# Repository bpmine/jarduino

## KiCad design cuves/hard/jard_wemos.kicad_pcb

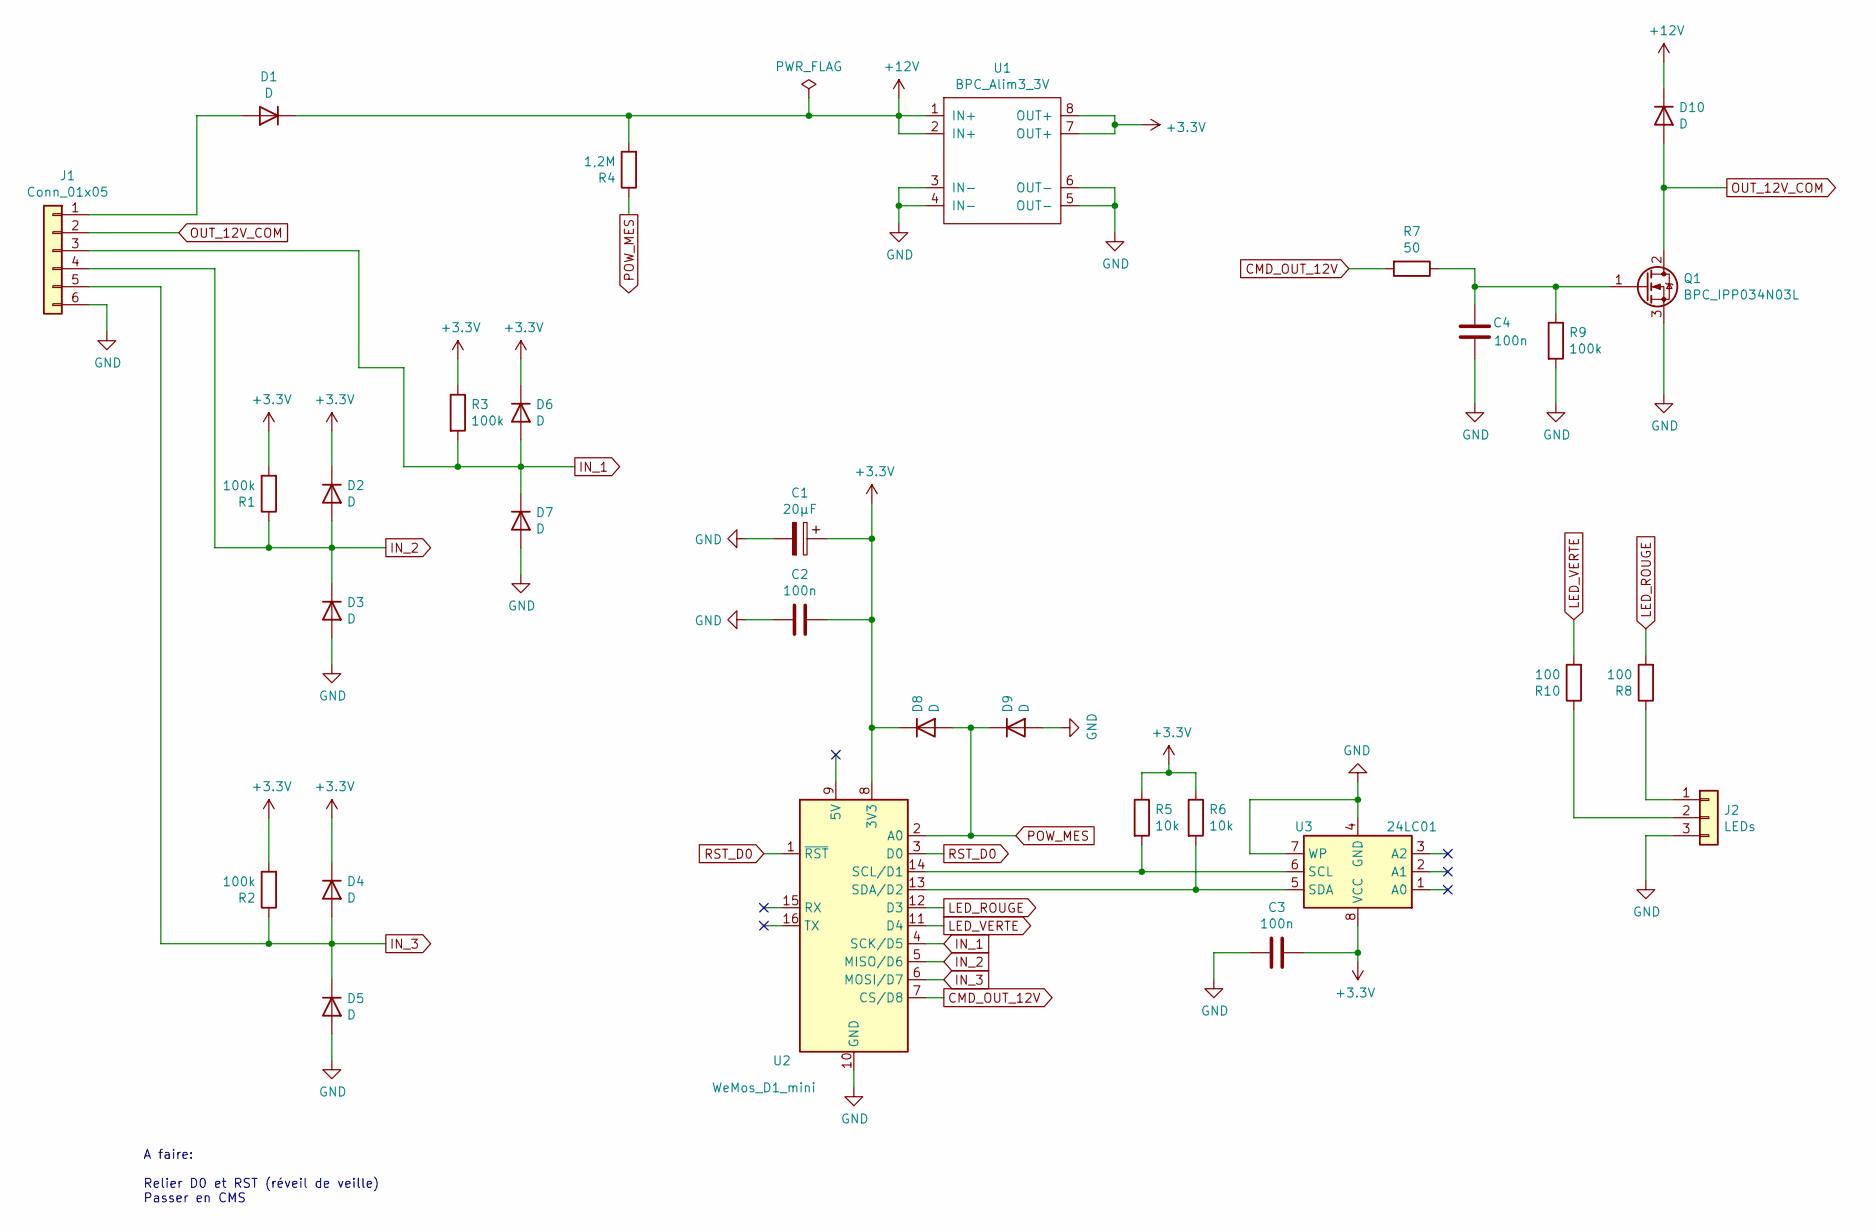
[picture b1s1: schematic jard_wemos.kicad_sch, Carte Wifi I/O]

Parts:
C1: 20µF; C_Radial_D6.3mm_H7.0mm_P2.50mm
C2, C3, C4: 100n; C_Disc_D3.0mm_W2.0mm_P2.50mm
D1, D2, D3, D4, D5, D6, D7, D8, D9, D10: D; D_A-405_P2.54mm_Vertical_KathodeUp
J1: Conn_01x05; TerminalBlock_Phoenix_MPT-0,5-6-2.54_1x06_P2.54mm_Horizontal
J2: LEDs; PinHeader_1x03_P2.54mm_Vertical
Q1: BPC_IPP034N03L; TO-220-3_Vertical
R1, R2, R3, R9: 100k; R_Axial_DIN0207_L6.3mm_D2.5mm_P2.54mm_Vertical
R4: 1,2M; R_Axial_DIN0207_L6.3mm_D2.5mm_P2.54mm_Vertical
R5, R6: 10k; R_Axial_DIN0207_L6.3mm_D2.5mm_P2.54mm_Vertical
R7: 50; R_Axial_DIN0207_L6.3mm_D2.5mm_P2.54mm_Vertical
R8, R10: 100; R_Axial_DIN0207_L6.3mm_D2.5mm_P2.54mm_Vertical
U1: BPC_Alim3_3V
U2: WeMos_D1_mini; WEMOS_D1_mini_light
U3: 24LC01; DIP-8_W7.62mm

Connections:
+3V3: C1.1, C2.1, C3.2, D2.1 (K), D4.1 (K), D6.1 (K), D8.1 (K), R1.2, R2.2, R3.1, R5.1, R6.1, U1.7 (OUT+), U1.8 (OUT+), U2.8 (3V3), U3.8 (VCC)
+12V: D1.1 (K), D10.1 (K), R4.2, U1.1 (IN+), U1.2 (IN+)
CMD_OUT_12V: R7.2, U2.7 (CS/D8)
GND: C1.2, C2.2, C3.1, C4.2, D3.2 (A), D5.2 (A), D7.2 (A), D9.2 (A), J1.6, J2.3, Q1.3 (S), R9.2, U1.3 (IN-), U1.4 (IN-), U1.5 (OUT-), U1.6 (OUT-), U2.10 (GND), U3.4 (GND), U3.7 (WP)
IN_1: D6.2 (A), D7.1 (K), J1.3, R3.2, U2.4 (SCK/D5)
IN_2: D2.2 (A), D3.1 (K), J1.4, R1.1, U2.5 (MISO/D6)
IN_3: D4.2 (A), D5.1 (K), J1.5, R2.1, U2.6 (MOSI/D7)
LED_ROUGE: R8.2, U2.12 (D3)
LED_VERTE: R10.2, U2.11 (D4)
unnamed: D1.2 (A), J1.1
unnamed: J2.1, R8.1
unnamed: J2.2, R10.1
unnamed: C4.1, Q1.1 (G), R7.1, R9.1
unnamed: R5.2, U2.14 (SCL/D1), U3.6 (SCL)
unnamed: R6.2, U2.13 (SDA/D2), U3.5 (SDA)
OUT_12V_COM: D10.2 (A), J1.2, Q1.2 (D)
POW_MES: D8.2 (A), D9.1 (K), R4.1, U2.2 (A0)
RST_D0: U2.1 (~RST), U2.3 (D0)

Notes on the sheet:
A faire: Relier D0 et RST (réveil de veille) Passer en CMS

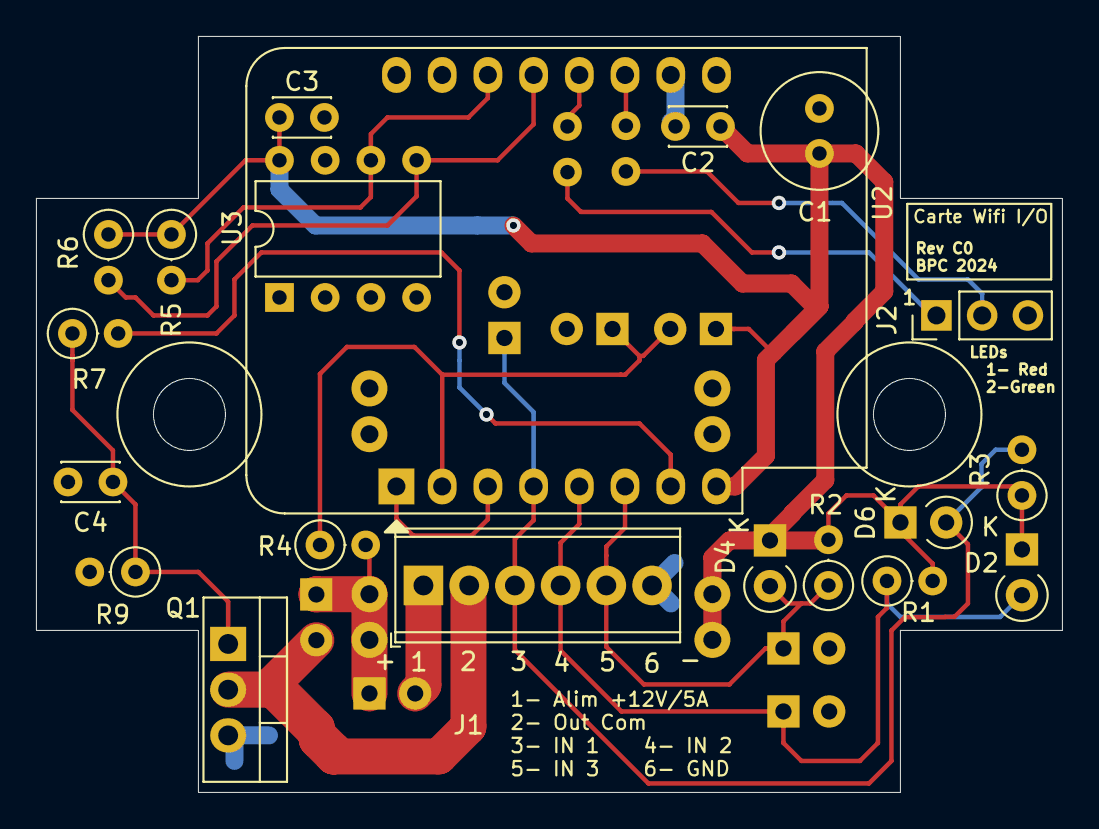
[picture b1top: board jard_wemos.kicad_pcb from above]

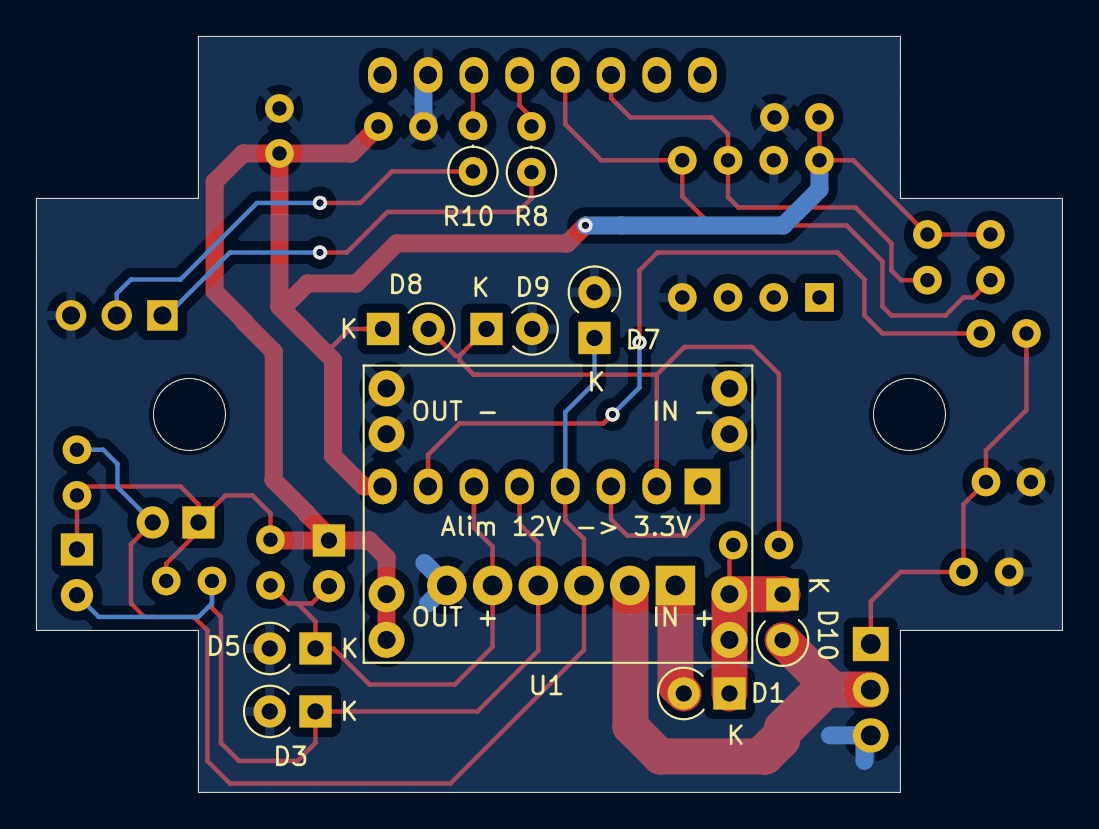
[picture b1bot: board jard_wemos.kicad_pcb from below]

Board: 2 copper layers, 57.0 x 42.0 mm, 30 parts (10 on the bottom side), 18 nets.

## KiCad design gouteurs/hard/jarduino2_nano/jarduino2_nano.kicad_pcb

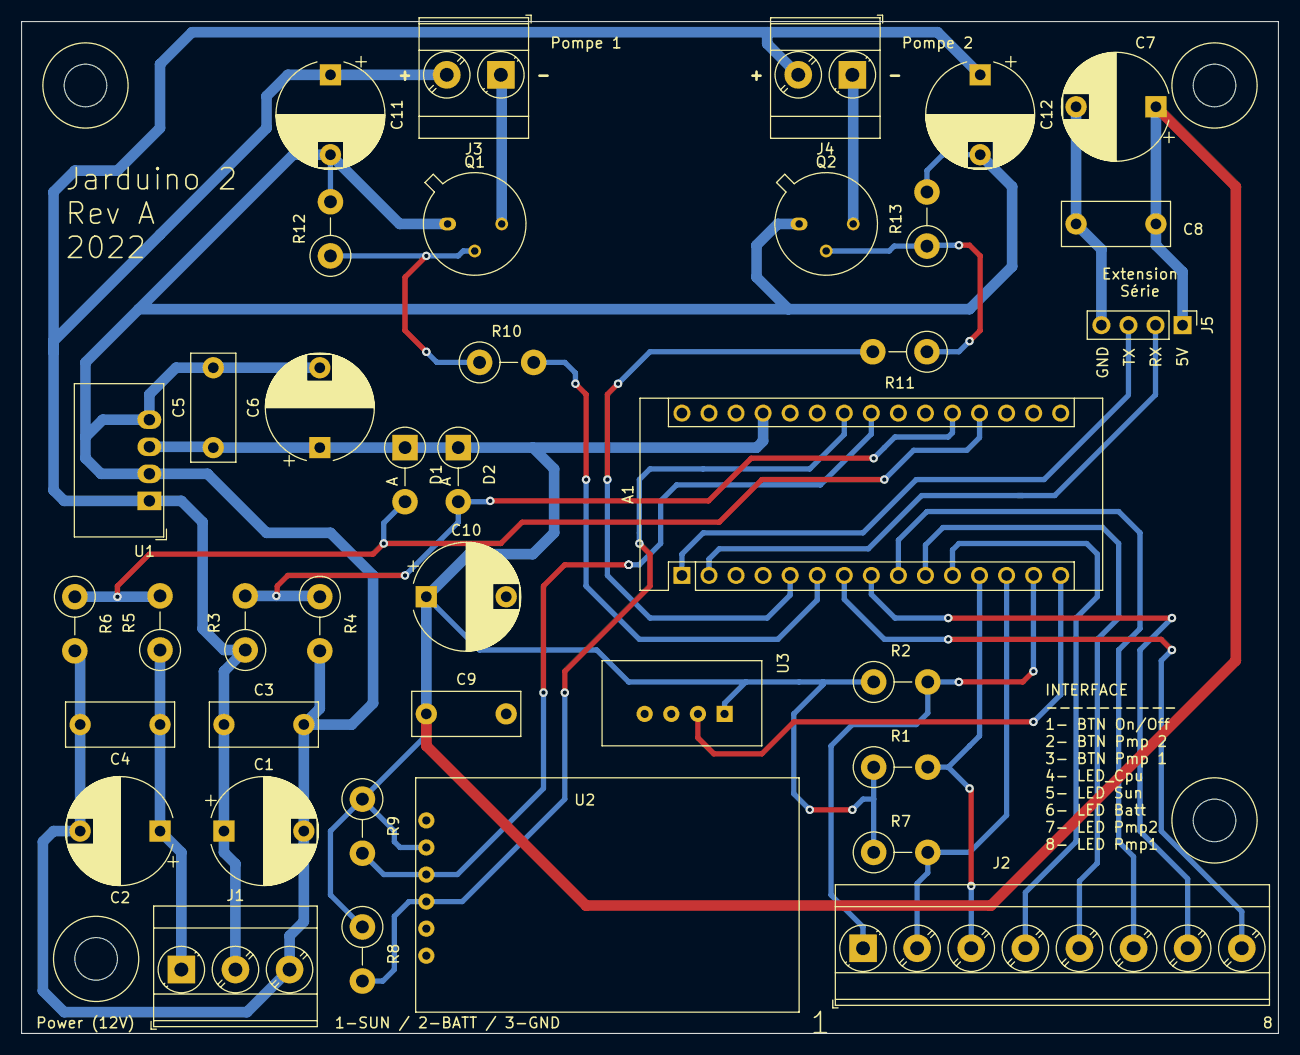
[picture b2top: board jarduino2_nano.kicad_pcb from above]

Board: 2 copper layers, 118.0 x 95.0 mm, 38 parts (0 on the bottom side), 25 nets.

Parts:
A1: Arduino_Nano_v3.x; BPC_Arduino_Nano
C1, C2, C6, C7, C10, C11, C12: 50µF / 50V; CP_Radial_D10.0mm_P7.50mm
C3, C4, C5, C8, C9: 1nF / 50V; C_Rect_L10.0mm_W4.0mm_P7.50mm_MKS4
D1, D2: D_Schottky; D_DO-15_P5.08mm_Vertical_AnodeUp
J1: Power; TerminalBlock_Phoenix_MKDS-3-3-5.08_1x03_P5.08mm_Horizontal
J2: Interface; TerminalBlock_Phoenix_MKDS-3-8-5.08_1x08_P5.08mm_Horizontal
J3: Pompe 1; TerminalBlock_Phoenix_MKDS-3-2-5.08_1x02_P5.08mm_Horizontal
J4: Pompe 2; TerminalBlock_Phoenix_MKDS-3-2-5.08_1x02_P5.08mm_Horizontal
J5: Ext Ser; PinHeader_1x04_P2.54mm_Vertical
Q1, Q2: Q_NPN_BCE; TO-39-3
R1, R2, R3, R5, R7, R12, R13: 100k; R_Axial_DIN0411_L9.9mm_D3.6mm_P5.08mm_Vertical
R4, R6: 40k; R_Axial_DIN0411_L9.9mm_D3.6mm_P5.08mm_Vertical
R8, R9: 10k; R_Axial_DIN0411_L9.9mm_D3.6mm_P5.08mm_Vertical
R10, R11: 220; R_Axial_DIN0411_L9.9mm_D3.6mm_P5.08mm_Vertical
U1: RFB-0505S; Converter_DCDC_Murata_MEE3SxxxxSC_THT
U2: RtcArduino; BPC_RtcArduino
U3: DHT22; BPC_DHT22

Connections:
+5V: A1.27, C5.1, C6.1, C7.1, C8.1, C9.1, C10.1, D1.1, D2.1, J5.1, R1.1, R2.1, R7.1, R8.1, R9.1, U1.3, U2.2, U3.1
+12V: C1.1, C3.1, C11.1, C12.1, J1.2, J3.2, J4.2, R3.1, U1.1
BTN_ONOFF: A1.14, J2.1, R2.2
BTN_PMP1: A1.12, J2.3, R1.2
BTN_PMP2: A1.13, J2.2, R7.2
CMD_PMP1: A1.6, R10.2
CMD_PMP2: A1.5, R11.2
GND: A1.4, A1.29, C1.2, C2.2, C3.2, C4.2, C5.2, C6.2, C7.2, C8.2, C9.2, C10.2, C11.2, C12.2, J1.3, J5.4, Q1.1, Q2.1, R4.2, R6.2, R12.2, R13.2, U1.2, U1.4, U2.1, U3.4
LED_12V_BATT: A1.9, J2.6
LED_12V_SUN: A1.10, J2.5
LED_CPU: A1.11, J2.4
LED_PMP1: A1.7, J2.8
LED_PMP2: A1.8, J2.7
unnamed: A1.1, J5.3
unnamed: A1.2, J5.2
unnamed: A1.15, U3.2
unnamed: C2.1, C4.1, J1.1, R5.1
unnamed: J3.1, Q1.3
unnamed: J4.1, Q2.3
unnamed: Q1.2, R10.1, R12.1
unnamed: Q2.2, R11.1, R13.1
POW_BATT: A1.20, D2.2, R3.2, R4.1
POW_SUN: A1.19, D1.2, R5.2, R6.1
SCL: A1.24, R8.2, U2.4
SDA: A1.23, R9.2, U2.3

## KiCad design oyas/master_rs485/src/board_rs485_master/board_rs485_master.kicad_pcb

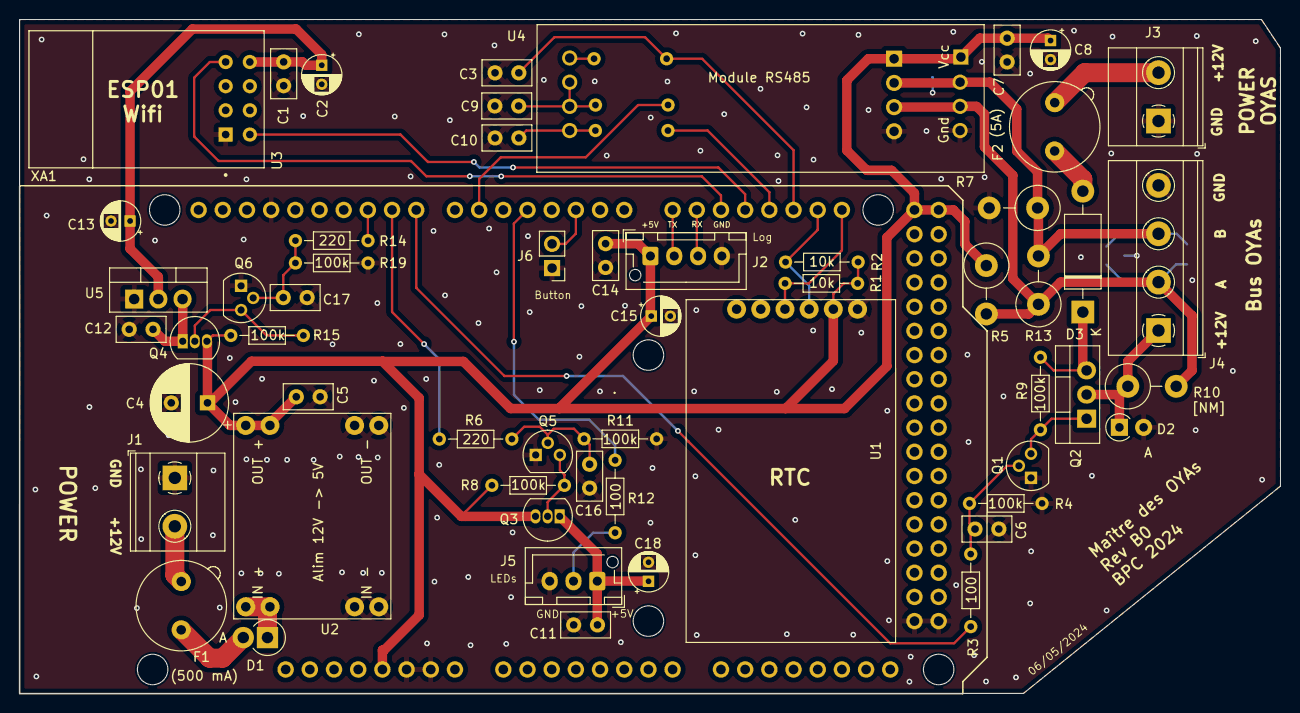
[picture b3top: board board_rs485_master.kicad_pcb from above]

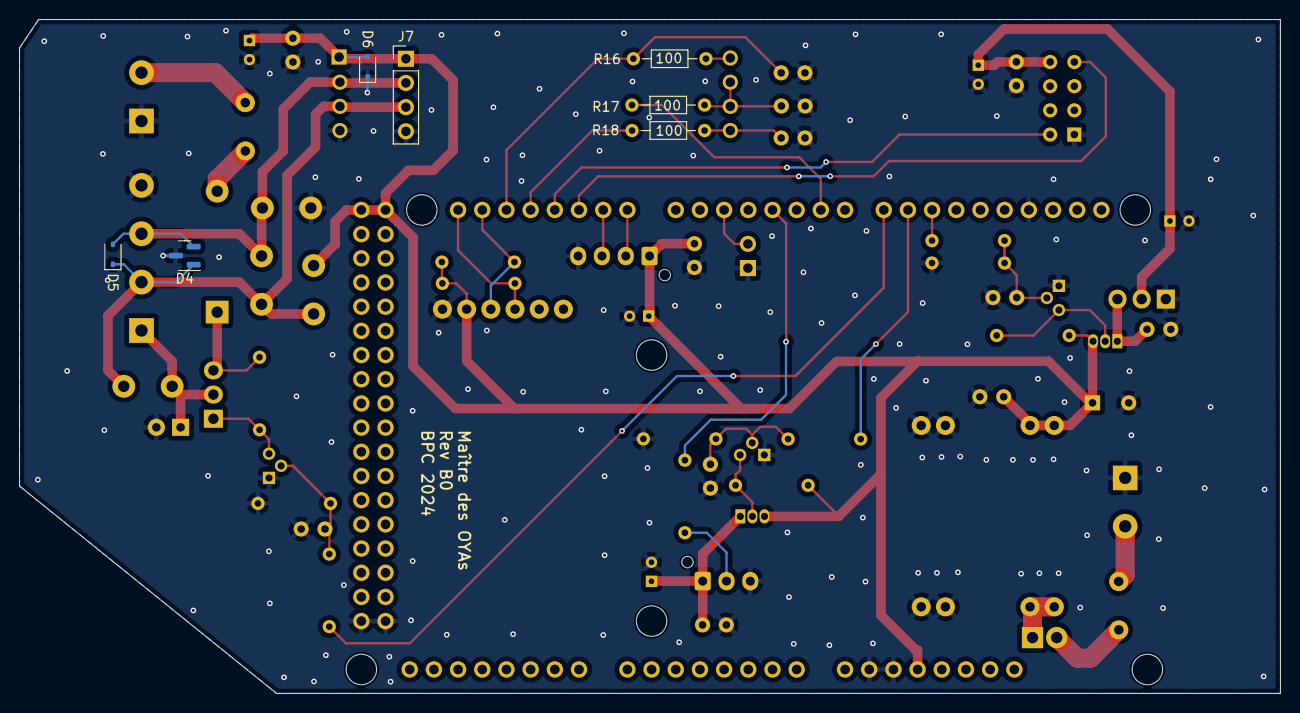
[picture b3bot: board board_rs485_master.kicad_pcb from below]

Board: 2 copper layers, 132.4 x 70.8 mm, 64 parts (7 on the bottom side), 38 nets.

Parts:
C1, C5, C6, C7, C11, C12, C14, C16, C17: 100nF; C_Disc_D5.0mm_W2.5mm_P2.50mm
C2, C8, C13, C15, C18: 10µF; CP_Radial_D4.0mm_P2.00mm
C3, C9, C10: 1nF; C_Disc_D5.0mm_W2.5mm_P2.50mm
C4: 100µF; CP_Radial_D8.0mm_P3.80mm
D1: SR560; D_DO-15_P2.54mm_Vertical_AnodeUp
D2: BAT42; D_A-405_P2.54mm_Vertical_AnodeUp
D3: SR560; D_DO-15_P12.70mm_Horizontal
D4: SM712_SOT23; SOT-23
D5, D6: SD12_SOD323; D_SOD-323
F1: 500 mA; Fuseholder_TR5_Littelfuse_No560_No460
F2: 5A; Fuseholder_TR5_Littelfuse_No560_No460
J1: POWER_12V; TerminalBlock_Phoenix_MKDS-1,5-2-5.08_1x02_P5.08mm_Horizont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
J2: Log; JST_XH_B4B-XH-AM_1x04_P2.50mm_Vertical
J3: POWER_OYAS_12V; TerminalBlock_Phoenix_MKDS-1,5-2-5.08_1x02_P5.08mm_Horizont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
J4: BUS_OYAS; TerminalBlock_Phoenix_MKDS-1,5-4-5.08_1x04_P5.08mm_Horizont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
J5: Leds RGB; JST_XH_B3B-XH-AM_1x03_P2.50mm_Vertical
J6: Button; PinHeader_1x02_P2.54mm_Vertical
J7: Adapt BUS; PinHeader_1x04_P2.54mm_Vertical
Q1, Q5, Q6: BPC_2N2222A; TO-92
Q2: P03P4L-04; TO-220-3_Vertical
Q3, Q4: BC327; TO-92_Inline
R1, R2: 10k; R_Axial_DIN0204_L3.6mm_D1.6mm_P7.62mm_Horizontal
R3, R12, R16, R17, R18: 100; R_Axial_DIN0204_L3.6mm_D1.6mm_P7.62mm_Horizontal
R4, R8, R9, R11, R15, R19: 100k; R_Axial_DIN0204_L3.6mm_D1.6mm_P7.62mm_Horizontal
R5, R7: 220; R_Axial_DIN0414_L11.9mm_D4.5mm_P5.08mm_Vertical
R6, R14: 220; R_Axial_DIN0204_L3.6mm_D1.6mm_P7.62mm_Horizontal
R10: R; R_Axial_DIN0414_L11.9mm_D4.5mm_P5.08mm_Vertical
R13: 128; R_Axial_DIN0414_L11.9mm_D4.5mm_P5.08mm_Vertical
U1: RtcArduino; BPC_RtcArduino
U2: BPC_Alim5V
U3: BPC_ESP8266-01_ESP-01; BPC_XCVR_ESP8266-01_ESP-01
U4: BPC_Mod485
U5: LM1117DT-3.3; TO-220-3_Vertical
XA1: Arduino_Mega2560_Shield; BPC_Arduino_Mega2560_Shield

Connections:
+5V: C4.1, C5.1, C7.1, C8.1, C14.1, C15.1, D6.2 (A2), J2.1, J7.1, Q3.3 (E), Q4.3 (E), R1.1, R2.1, R5.1, R8.1, R15.1, U1.2 (VCC), U2.7 (OUT+), U2.8 (OUT+), U4.1 (Vcc), XA1.5V1 (5V), XA1.5V3 (5V), XA1.5V4 (5V)
A: D4.1 (A1), D5.1 (A1), J4.2, J7.3, R5.2, R10.2, R13.1, U4.3 (A)
B: D4.2 (A2), D5.2 (A2), J4.3, J7.2, R7.1, R13.2, U4.2 (B)
CMD_LEDS_PWR: R6.1, XA1.D9
CMD_OYAS_PWR: R3.2, XA1.D8
CMD_WIFI_PWR: R14.1, XA1.D10
DATA_LEDS: R12.1, XA1.D4
GND: C1.2, C2.2, C3.2, C4.2, C5.2, C6.2, C7.2, C8.2, C9.2, C10.2, C11.2, C12.2, C13.2, C14.2, C15.2, C16.2, C17.2, C18.2, D2.2 (A), D4.3 (common), D6.1 (A1), J1.1, J2.4, J3.1, J4.4, J5.3, J6.1, J7.4, Q1.1, Q5.1, Q6.1, R4.2, R7.2, R11.2, R19.2, U1.1 (GND), U2.3 (IN-), U2.4 (IN-), U2.5 (OUT-), U2.6 (OUT-), U3.1 (GND), U4.4 (Gnd), U5.1 (GND), XA1.GND1 (GND), XA1.GND2 (GND), XA1.GND3 (GND), XA1.GND5 (GND), XA1.GND6 (GND)
unnamed: C6.1, Q1.2, R3.1, R4.1
unnamed: C16.1, Q5.2, R6.2, R11.1
unnamed: C17.1, Q6.2, R14.2, R19.1
unnamed: D1.2 (A), F1.1
unnamed: D1.1 (K), U2.1 (IN+), U2.2 (IN+)
unnamed: D2.1 (K), J4.1, Q2.2 (D), R10.1
unnamed: D3.2 (A), F2.1
unnamed: D3.1 (K), Q2.3 (S), R9.1
unnamed: F1.2, J1.2
unnamed: F2.2, J3.2
unnamed: C11.1, C18.1, J5.1, Q3.1 (C)
unnamed: J5.2, R12.2
unnamed: Q1.3, Q2.1 (G), R9.2
unnamed: Q3.2 (B), Q5.3, R8.2
unnamed: Q4.2 (B), Q6.3, R15.2
unnamed: C12.1, Q4.1 (C), U5.3 (VI)
unnamed: C9.1, R17.1, U4.6 (DE), U4.7 (RE)
unnamed: C10.1, R18.1, U4.5 (DI)
unnamed: R16.1, U4.8 (RO)
POWER_3.3: C1.1, C2.1, C13.1, U3.8 (VCC), U5.2 (VO)
RS485_RX: C3.1, R16.2, XA1.D19 (D19_RX1)
RS485_TX: R18.2, XA1.D18 (D18_TX1)
RX_LOG: J2.3, XA1.D15 (D15_RX3)
RX_WIFI: U3.5 (TXD), XA1.D17 (D17_RX2)
SCL: R1.2, U1.4 (SCL), XA1.D21 (D21_SCL)
SDA: R2.2, U1.3 (SDA), XA1.D20 (D20_SDA)
TEST_BTN: J6.2, XA1.D2 (D2_INT0)
TX_EN: R17.2, XA1.D6
TX_LOG: J2.2, XA1.D14 (D14_TX3)
TX_WIFI: U3.4 (RXD), XA1.D16 (D16_TX2)

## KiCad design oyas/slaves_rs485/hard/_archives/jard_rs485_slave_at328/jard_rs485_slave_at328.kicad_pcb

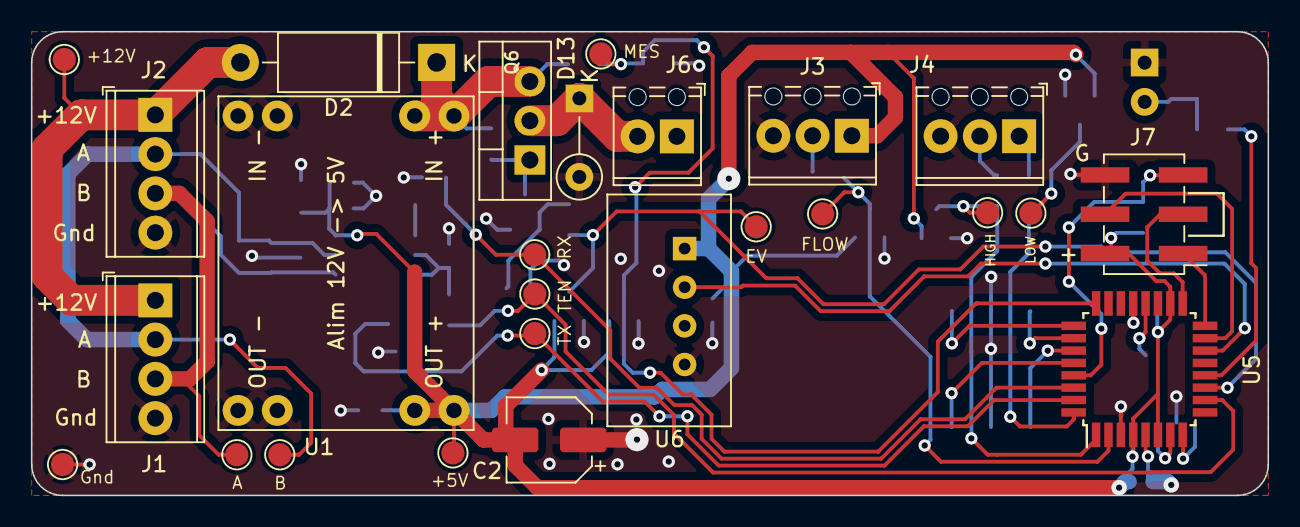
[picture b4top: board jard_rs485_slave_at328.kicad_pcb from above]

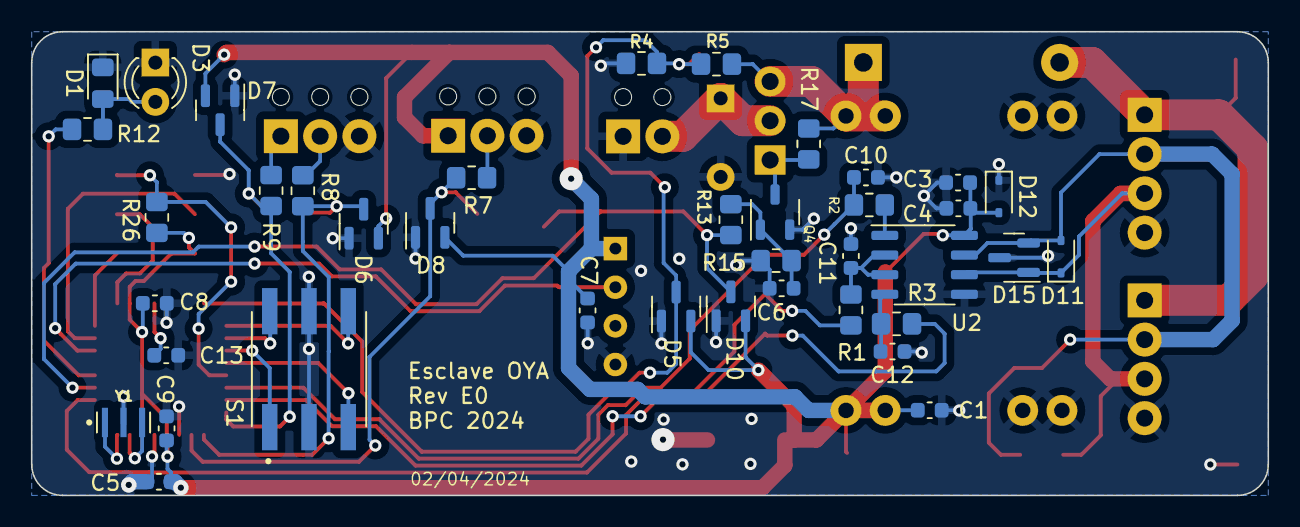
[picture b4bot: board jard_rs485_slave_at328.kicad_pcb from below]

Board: 2 copper layers, 80.0 x 30.0 mm, 65 parts (39 on the bottom side), 37 nets.

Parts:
C1, C4, C7, C9, C10, C11, C12: 1nF; C_0603_1608Metric
C2: 10µF; CP_Elec_5x5.9
C3, C5, C6, C8, C13: 100nF; C_0603_1608Metric
D1: LED; LED_0805_2012Metric_Pad1.15x1.40mm_HandSolder
D2: SR560; D_DO-15_P12.70mm_Horizontal
D3: LED; LED_D3.0mm_FlatTop
D5, D6, D7, D8, D10: BAV99; SOT-23
D11, D12: SD12_SOD323; D_SOD-323
D13: 1N4007G; D_A-405_P5.08mm_Vertical_KathodeUp
D15: SM712_SOT23; SOT-23
J1: BUS_IN; TerminalBlock_Phoenix_MPT-0,5-4-2.54_1x04_P2.54mm_Horizontal
J2: BUS_OUT; TerminalBlock_Phoenix_MPT-0,5-4-2.54_1x04_P2.54mm_Horizontal
J3: Débit; TerminalBlock_Phoenix_MPT-0,5-3-2.54_1x03_P2.54mm_Horizontal
J4: Niveaux; TerminalBlock_Phoenix_MPT-0,5-3-2.54_1x03_P2.54mm_Horizontal
J6: EV1; TerminalBlock_Phoenix_MPT-0,5-2-2.54_1x02_P2.54mm_Horizontal
J7: ISCP; BPC_ISCP_CMS
Q4: BPC_FMMT38C; BPC_SOT-23-3
Q6: P03P4L-04; TO-220-3_Vertical
R1, R2, R3, R7, R8, R9: 100; R_0805_2012Metric_Pad1.20x1.40mm_HandSolder
R4: 40k; R_0805_2012Metric_Pad1.20x1.40mm_HandSolder
R5, R15, R17: 100k; R_0805_2012Metric_Pad1.20x1.40mm_HandSolder
R12, R13: 220; R_0805_2012Metric_Pad1.20x1.40mm_HandSolder
R26: 1k; R_0805_2012Metric_Pad1.20x1.40mm_HandSolder
S1: RDS-16S-74385-SMT; BPC_RDS-16S-74385-SMT
TP1, TP2, TP3, TP4, TP6, TP7, TP8, TP9, TP10, TP11, TP12, TP13, TP15: TestPoint; TestPoint_Pad_D1.5mm
U1: BPC_Alim5V
U2: MAX485E; SO-8_3.9x4.9mm_P1.27mm
U5: ATmega328P-A; TQFP-32_7x7mm_P0.8mm
U6: BPC_DHT22
Y1: Resonator; BPC_16MHz_CSTNE16M0V530000R0

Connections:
+5V: C1.1, C2.2, C3.1, C4.1, C5.2, C7.1, C8.2, C9.2, D5.2 (A), D6.2 (A), D7.2 (A), D8.2 (A), D10.2 (A), D12.2 (A2), J3.1, J7.2 (VCC), R26.2, TP8.1, U1.7 (OUT+), U1.8 (OUT+), U2.8 (VCC), U5.4 (VCC), U5.6 (VCC), U5.18 (AVCC), U6.1 (VDD)
A1: S1.1, U5.27 (PC4)
A2: S1.2, U5.25 (PC2)
A3: S1.4, U5.28 (PC5)
A4: S1.8, U5.26 (PC3)
BUS_A: D11.2 (A2), D15.2 (A2), J1.2, J2.2, TP6.1, U2.7 (B)
BUS_B: D11.1 (A1), D15.1 (A1), J1.3, J2.3, TP3.1, U2.6 (A)
CMD_EV1: D10.3 (K), R13.1, TP15.1, U5.11 (PD7)
FLOW: D8.3 (K), R7.2, TP11.1, U5.2 (PD4)
GND: C1.2, C2.1, C3.2, C4.2, C5.1, C6.2, C7.2, C8.1, C9.1, C10.2, C11.2, C12.2, C13.1, D1.1 (K), D3.1 (K), D5.1 (K), D6.1 (K), D7.1 (K), D8.1 (K), D10.1 (K), D12.1 (A1), D13.2 (A), D15.3 (common), J1.4, J2.4, J3.3, J4.3, J6.1, J7.6 (GND), Q4.2 (E), R4.1, R15.2, S1.C_1 (C), S1.C_2 (C), TP10.1, U1.3 (IN-), U1.4 (IN-), U1.5 (OUT-), U1.6 (OUT-), U2.5 (GND), U5.3 (GND), U5.5 (GND), U5.21 (GND), U6.4 (GND), Y1.2
LVL_HIGH: D6.3 (K), R8.2, TP12.1, U5.1 (PD3)
LVL_LOW: D7.3 (K), R9.2, TP13.1, U5.32 (PD2)
MISO: J7.1 (MISO), U5.16 (PB4)
MOSI: J7.4 (MOSI), U5.15 (PB3)
unnamed: D1.2 (A), D3.2 (A), R12.2
unnamed: D2.2 (A), J1.1, J2.1, TP2.1
unnamed: D13.1 (K), J6.2, Q6.2 (D)
unnamed: J3.2, R7.1
unnamed: J4.1, R9.1
unnamed: J4.2, R8.1
unnamed: C6.1, Q4.1 (B), R13.2, R15.1
unnamed: Q4.3 (C), Q6.1 (G), R17.2
unnamed: C11.1, R1.2, U2.2 (~RE), U2.3 (DE)
unnamed: C12.1, R3.2, U2.4 (DI)
unnamed: R2.2, U2.1 (RO)
unnamed: C13.2, U5.20 (AREF)
unnamed: R12.1, U5.12 (PB0)
unnamed: U5.7 (XTAL1/PB6), Y1.3
unnamed: U5.8 (XTAL2/PB7), Y1.1
POWER_12V: D2.1 (K), Q6.3 (S), R5.2, R17.1, U1.1 (IN+), U1.2 (IN+)
POW_MES: D5.3 (K), R4.2, R5.1, TP9.1, U5.24 (PC1)
RESET: J7.5 (RST), R26.1, U5.29 (~RESET/PC6)
RX: C10.1, R2.1, TP1.1, U5.30 (PD0)
SCK: J7.3 (SCK), U5.17 (PB5)
TEMP: U5.14 (PB2), U6.2 (DATA)
TX: R3.1, TP7.1, U5.31 (PD1)
TX_EN: R1.1, TP4.1, U5.10 (PD6)

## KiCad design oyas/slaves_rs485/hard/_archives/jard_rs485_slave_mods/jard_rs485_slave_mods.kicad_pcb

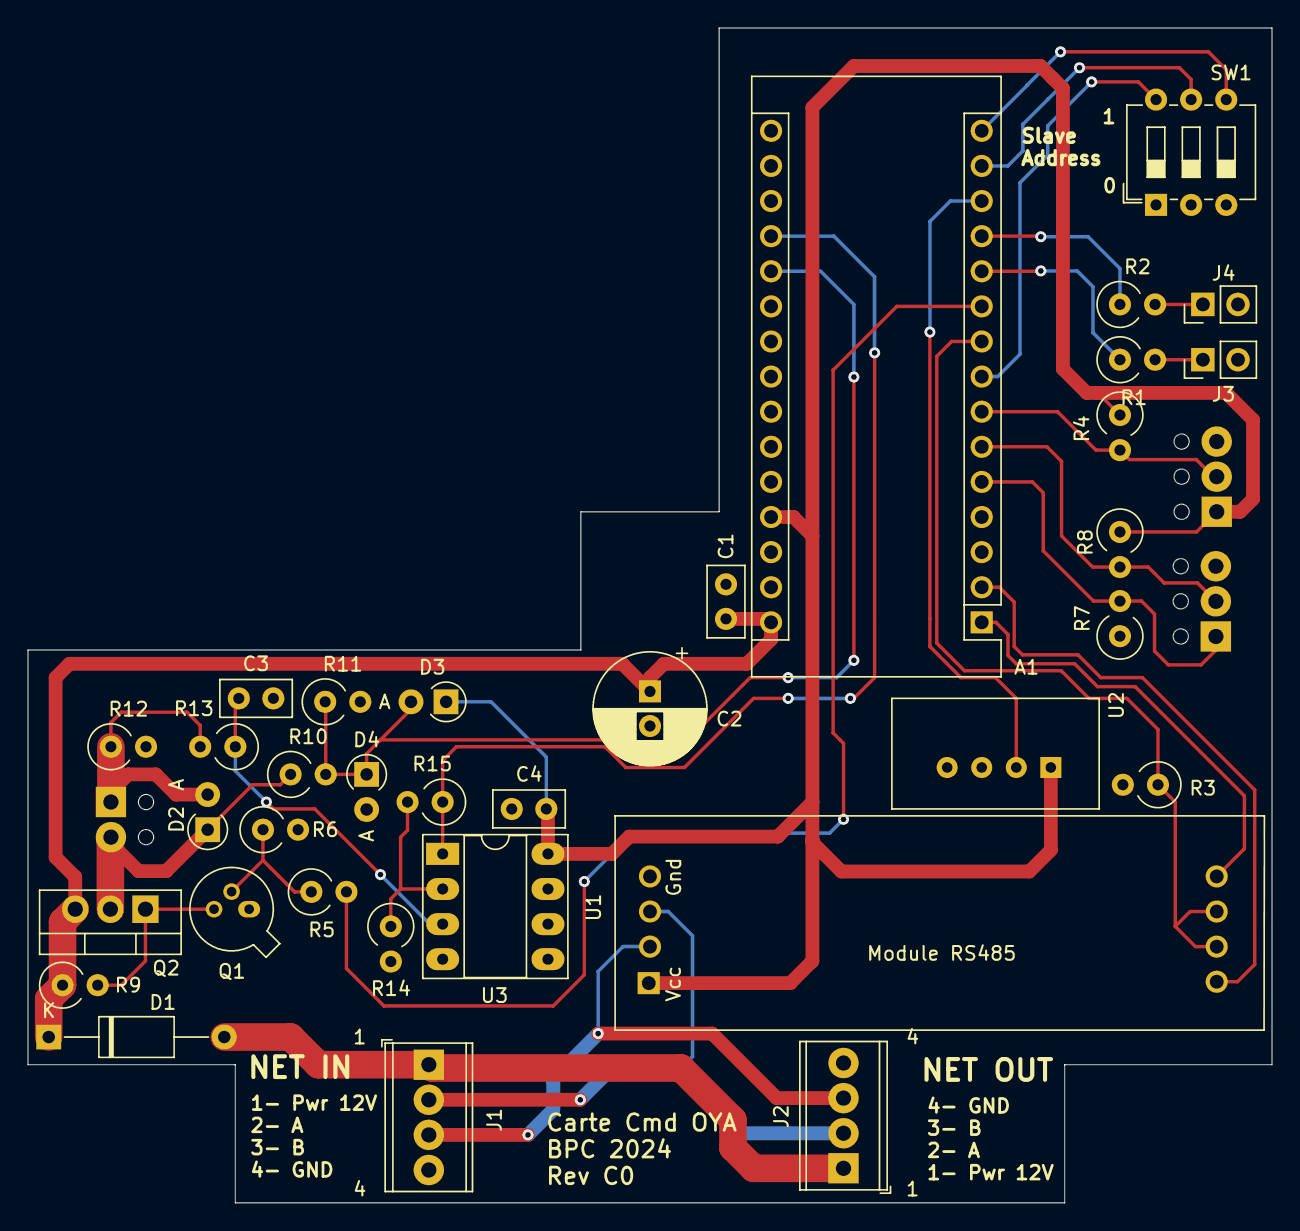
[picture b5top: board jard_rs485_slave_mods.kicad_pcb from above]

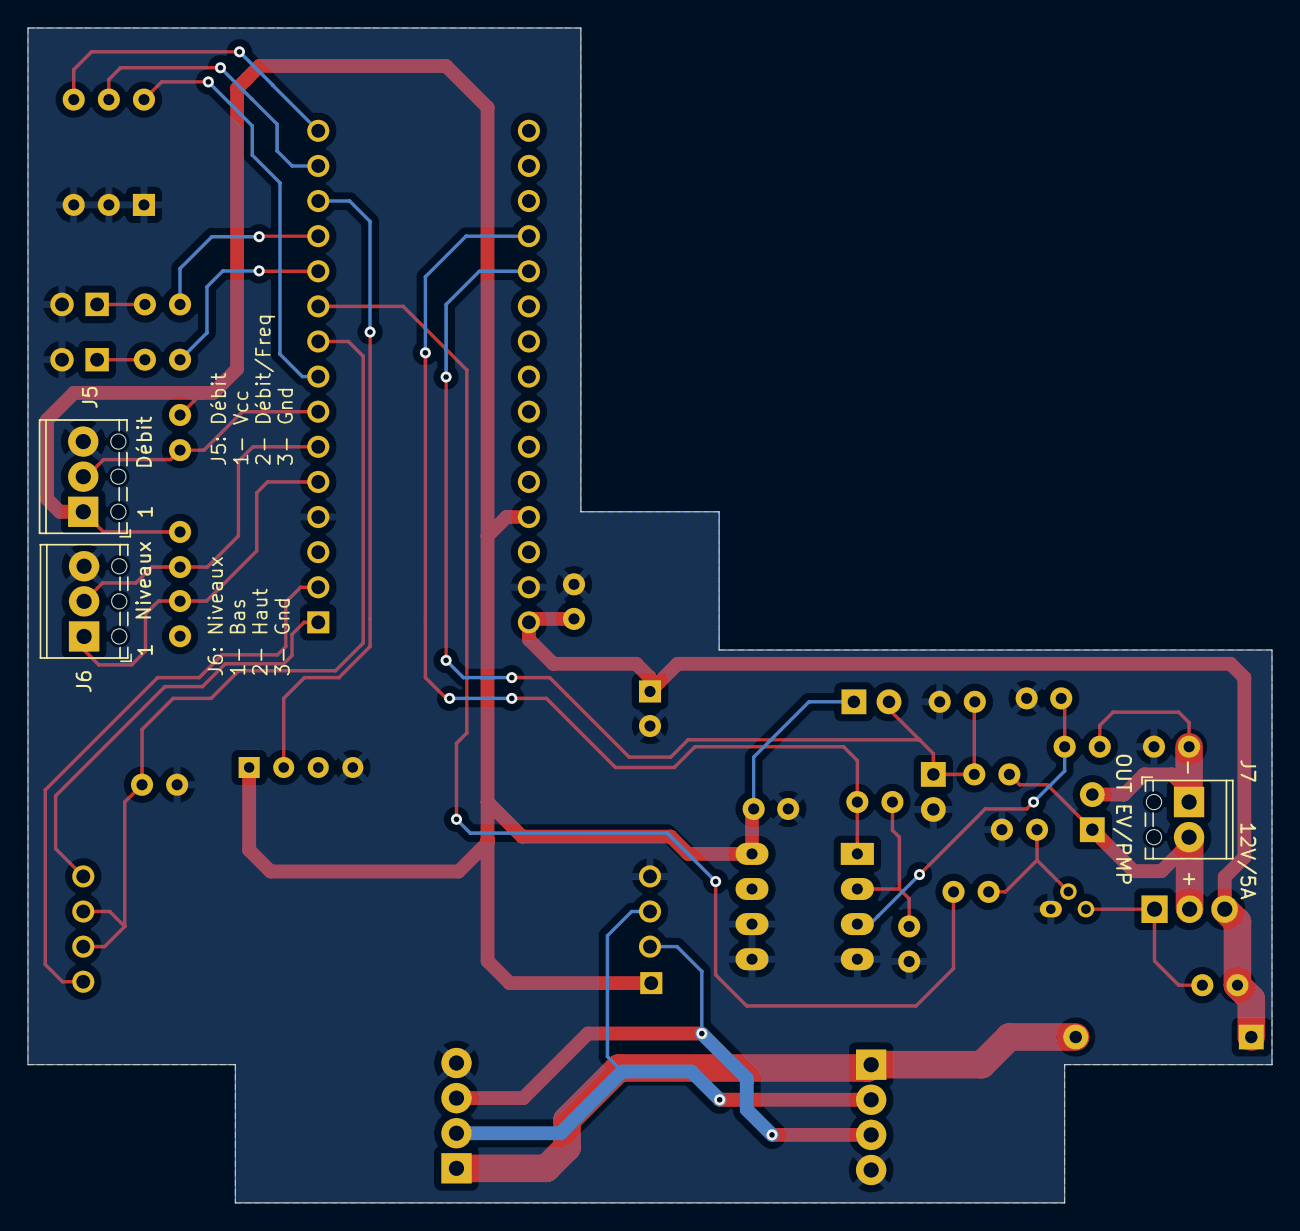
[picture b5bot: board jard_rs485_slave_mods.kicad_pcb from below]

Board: 2 copper layers, 90.0 x 85.0 mm, 37 parts (3 on the bottom side), 29 nets.

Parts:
A1: Arduino_Nano_v2.x; BPC_Arduino_Nano
C1: 10n; C_Disc_D5.0mm_W2.5mm_P2.50mm
C2: 10µF; CP_Radial_D8.0mm_P2.50mm
C3, C4: 100n; C_Disc_D5.0mm_W2.5mm_P2.50mm
D1: D; D_A-405_P12.70mm_Horizontal
D2, D3, D4: D; D_A-405_P2.54mm_Vertical_AnodeUp
J1: NETWORK IN; TerminalBlock_Phoenix_MPT-0,5-4-2.54_1x04_P2.54mm_Horizontal
J2: NETWORK OUT; TerminalBlock_Phoenix_MPT-0,5-4-2.54_1x04_P2.54mm_Horizontal
J3, J4: LED; PinHeader_1x02_P2.54mm_Vertical
J5: Debit; TerminalBlock_Phoenix_MPT-0,5-3-2.54_1x03_P2.54mm_Horizontal
J6: Niveau; TerminalBlock_Phoenix_MPT-0,5-3-2.54_1x03_P2.54mm_Horizontal
J7: Electrovanne 12V; TerminalBlock_Phoenix_MPT-0,5-2-2.54_1x02_P2.54mm_Horizontal
Q1: BPC_2N2222A; TO-18-3
Q2: P03P4L-04; TO-220-3_Vertical
R1, R2: 150; R_Axial_DIN0309_L9.0mm_D3.2mm_P2.54mm_Vertical
R3, R4, R6, R7, R8, R9, R10: 100k; R_Axial_DIN0309_L9.0mm_D3.2mm_P2.54mm_Vertical
R5: 100; R_Axial_DIN0309_L9.0mm_D3.2mm_P2.54mm_Vertical
R11: 40k; R_Axial_DIN0309_L9.0mm_D3.2mm_P2.54mm_Vertical
R12: 30mR; R_Axial_DIN0309_L9.0mm_D3.2mm_P2.54mm_Vertical
R13: 10k; R_Axial_DIN0309_L9.0mm_D3.2mm_P2.54mm_Vertical
R14: 1k; R_Axial_DIN0309_L9.0mm_D3.2mm_P2.54mm_Vertical
R15: 32k; R_Axial_DIN0309_L9.0mm_D3.2mm_P2.54mm_Vertical
SW1: Address; SW_DIP_SPSTx03_Slide_6.7x9.18mm_W7.62mm_P2.54mm_LowProfile
U1: BPC_Mod485
U2: BPC_DHT22
U3: LM358; DIP-8_W7.62mm_Socket_LongPads

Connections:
CMD_EV: A1.10 (D7), R5.2
FLOW_IN: A1.7 (D4), J5.2, R4.2
GND: A1.4 (GND), A1.29 (GND), C1.1, C2.2, C3.1, C4.1, D4.2 (A), J1.4, J2.4, J3.2, J4.2, J5.3, J6.3, Q1.1, R3.2, R6.2, R11.2, R12.2, R14.2, SW1.1, SW1.2, SW1.3, U1.4 (Gnd), U2.4 (GND), U3.4 (V-), U3.5 (+), U3.6 (-)
IN_LVL_HIGH: A1.6 (D3), J6.2, R8.2
IN_LVL_LOW: A1.5 (D2), J6.1, R7.2
LED1: A1.11 (D8), R1.1
LED2: A1.12 (D9), R2.1
MES_I: A1.19 (A0), R15.1, U3.1
MES_V: A1.20 (A1), D3.2 (A), D4.1 (K), R10.2, R11.1
unnamed: A1.8 (D5), SW1.6
unnamed: A1.14 (D11), SW1.5
unnamed: A1.15 (D12), SW1.4
unnamed: A1.30 (VIN), C1.2, C2.1, D1.1 (K), Q2.3 (S), R9.1
unnamed: D1.2 (A), J1.1, J2.1
unnamed: D2.2 (A), J7.1, R12.1, R13.2
unnamed: D2.1 (K), J7.2, Q2.2 (D), R10.1
unnamed: J1.2, J2.2, U1.3 (A)
unnamed: J1.3, J2.3, U1.2 (B)
unnamed: J3.1, R1.2
unnamed: J4.1, R2.2
unnamed: Q1.2, R5.1, R6.1
unnamed: Q1.3, Q2.1 (G), R9.2
unnamed: C3.2, R13.1, U3.3 (+)
unnamed: R14.1, R15.2, U3.2 (-)
RX: A1.2 (D0/RX), U1.8 (RO)
TEMP: A1.13 (D10), U2.2 (DATA)
TX: A1.1 (D1/TX), U1.5 (DI)
TXEN: A1.9 (D6), R3.1, U1.6 (DE), U1.7 (RE)
Vcc: A1.27 (+5V), C4.2, D3.1 (K), J5.1, R4.1, R7.1, R8.1, U1.1 (Vcc), U2.1 (VDD), U3.8 (V+)

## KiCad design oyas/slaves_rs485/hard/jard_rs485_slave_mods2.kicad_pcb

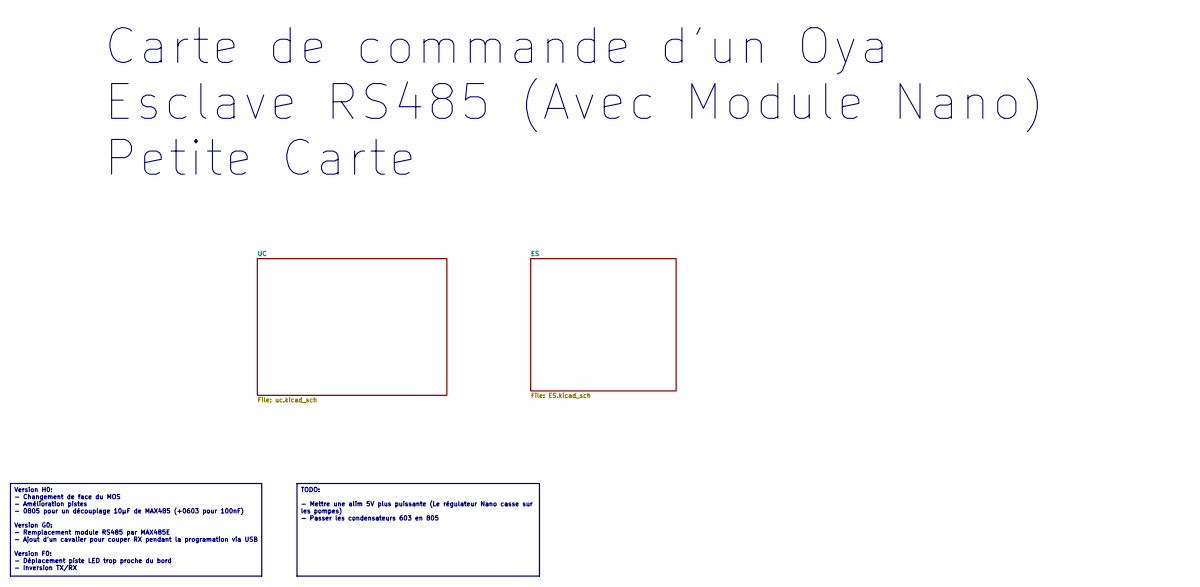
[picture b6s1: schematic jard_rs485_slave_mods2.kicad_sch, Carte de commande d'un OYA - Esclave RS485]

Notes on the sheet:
Version H0: - Changement de face du MOS - Amélioration pistes - 0805 pour un découplage 10µF de MAX485 (+0603 pour 100nF) Version G0: - Remplacement module RS485 par MAX485E - Ajout d'un cavalier pour couper RX pendant la programation via USB Version F0: - Déplacement piste LED trop proche du bord 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
TODO: - Mettre une alim 5V plus puissante (Le régulateur Nano casse sur les pompes) - Passer les condensateurs 603 en 805
Carte de commande d'un Oya Esclave RS485 (Avec Module Nano) Petite Carte
